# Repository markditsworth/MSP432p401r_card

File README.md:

# MSP432p401r Card

### PCB for a vertically mounted MSP432p401r chip

Uses the Samtec MECF-50-01-L-DV polarized edge connector, or equivalent.

1.6mm board thickness.

Supports GPIO ports 1 through 6.

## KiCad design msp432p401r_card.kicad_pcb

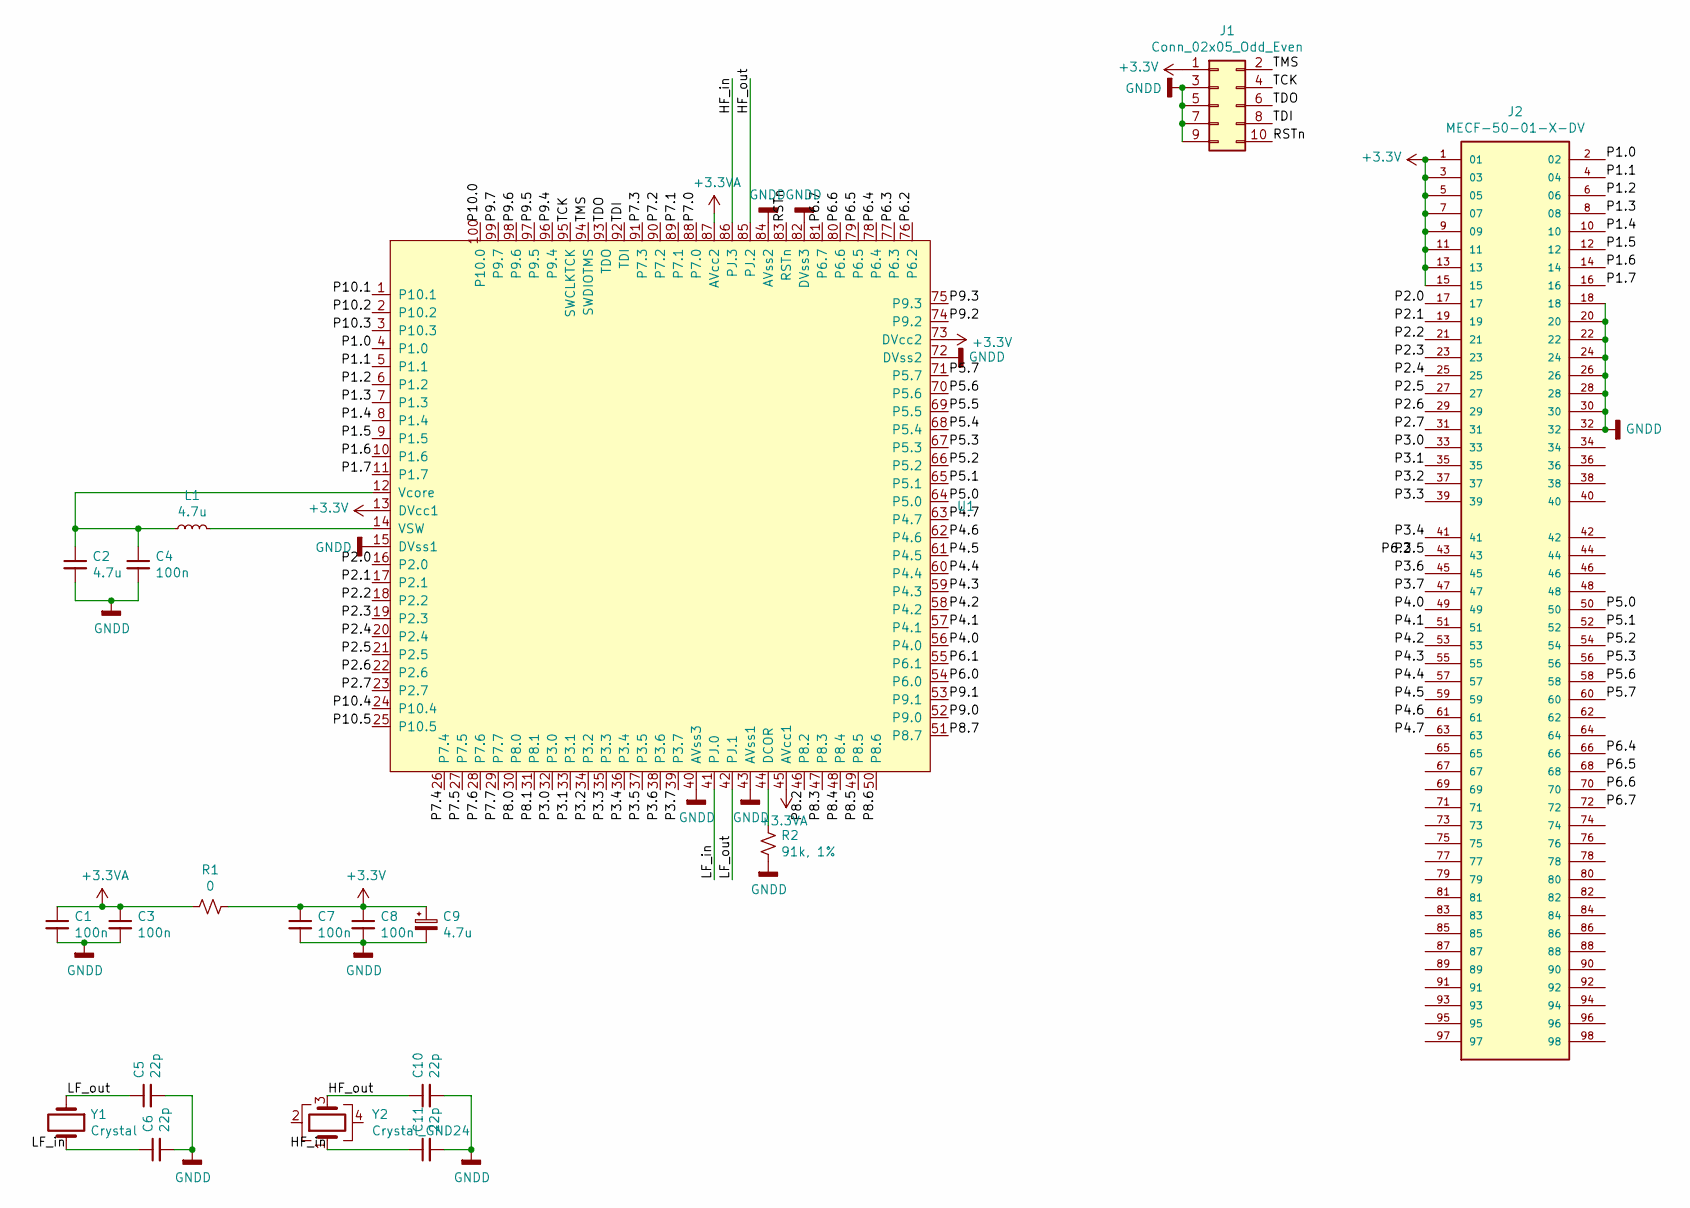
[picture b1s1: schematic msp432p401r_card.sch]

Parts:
C1, C3, C4, C7, C8: 100n; C_0402_1005Metric
C2, C9: 4.7u; C_1206_3216Metric
C5, C6, C10, C11: 22p; C_0402_1005Metric
J1: Conn_02x05_Odd_Even; Samtec_HLE-105-02-xx-DV-TE_2x05_P2.54mm_Horizontal
J2: MECF-50-01-X-DV; Samtec_MECF-50-0_-L-DV_2x50_P1.27mm_Polarized_Edge; PARTREV D
L1: 4.7u; L_2010_5025Metric; Part No LQM21PN4R7NGR
R1: 0; R_1206_3216Metric
R2: 91k, 1%; R_1206_3216Metric
U1: MSP432p401r_chip; LQFP-100_14x14mm_P0.5mm
Y1: Crystal; Crystal_SMD_MicroCrystal_MS3V-T1R
Y2: Crystal_GND24; Crystal_SMD_SeikoEpson_FA238-4Pin_3.2x2.5mm_HandSoldering

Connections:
+3.3VA: C1.1, C3.1, R1.2, U1.45 (AVcc1), U1.87 (AVcc2)
+3V3: C7.1, C8.1, C9.1, J1.1, J2.1, J2.3, J2.5, J2.7, J2.9, J2.11, J2.13, J2.15, R1.1, U1.13 (DVcc1), U1.73 (DVcc2)
/HF_in: C11.1, U1.86 (PJ.3), Y2.1
/HF_out: C10.1, U1.85 (PJ.2), Y2.3
/LF_in: C6.1, U1.41 (PJ.0), Y1.2
/LF_out: C5.1, U1.42 (PJ.1), Y1.1
/P1.0: J2.2, U1.4 (P1.0)
/P1.1: J2.4, U1.5 (P1.1)
/P1.2: J2.6, U1.6 (P1.2)
/P1.3: J2.8, U1.7 (P1.3)
/P1.4: J2.10, U1.8 (P1.4)
/P1.5: J2.12, U1.9 (P1.5)
/P1.6: J2.14, U1.10 (P1.6)
/P1.7: J2.16, U1.11 (P1.7)
/P2.0: J2.17, U1.16 (P2.0)
/P2.1: J2.19, U1.17 (P2.1)
/P2.2: J2.21, U1.18 (P2.2)
/P2.3: J2.23, U1.19 (P2.3)
/P2.4: J2.25, U1.20 (P2.4)
/P2.5: J2.27, U1.21 (P2.5)
/P2.6: J2.29, U1.22 (P2.6)
/P2.7: J2.31, U1.23 (P2.7)
/P3.0: J2.33, U1.32 (P3.0)
/P3.1: J2.35, U1.33 (P3.1)
/P3.2: J2.37, U1.34 (P3.2)
/P3.3: J2.39, U1.35 (P3.3)
/P3.4: J2.41, U1.36 (P3.4)
/P3.5: J2.43, U1.37 (P3.5)
/P3.6: J2.45, U1.38 (P3.6)
/P3.7: J2.47, U1.39 (P3.7)
/P4.0: J2.49, U1.56 (P4.0)
/P4.1: J2.51, U1.57 (P4.1)
/P4.2: J2.53, U1.58 (P4.2)
/P4.3: J2.55, U1.59 (P4.3)
/P4.4: J2.57, U1.60 (P4.4)
/P4.5: J2.59, U1.61 (P4.5)
/P4.6: J2.61, U1.62 (P4.6)
/P4.7: J2.63, U1.63 (P4.7)
/P5.0: J2.50, U1.64 (P5.0)
/P5.1: J2.52, U1.65 (P5.1)
/P5.2: J2.54, U1.66 (P5.2)
/P5.3: J2.56, U1.67 (P5.3)
/P5.4: U1.68 (P5.4)
/P5.5: U1.69 (P5.5)
/P5.6: J2.58, U1.70 (P5.6)
/P5.7: J2.60, U1.71 (P5.7)
/P6.0: U1.54 (P6.0)
/P6.1: U1.55 (P6.1)
/P6.2: U1.76 (P6.2)
/P6.3: U1.77 (P6.3)
/P6.4: J2.66, U1.78 (P6.4)
/P6.5: J2.68, U1.79 (P6.5)
/P6.6: J2.70, U1.80 (P6.6)
/P6.7: J2.72, U1.81 (P6.7)
/P7.0: U1.88 (P7.0)
/P7.1: U1.89 (P7.1)
/P7.2: U1.90 (P7.2)
/P7.3: U1.91 (P7.3)
/P7.4: U1.26 (P7.4)
/P7.5: U1.27 (P7.5)
/P7.6: U1.28 (P7.6)
/P7.7: U1.29 (P7.7)
/P8.0: U1.30 (P8.0)
/P8.1: U1.31 (P8.1)
/P8.2: U1.46 (P8.2)
/P8.3: U1.47 (P8.3)
/P8.4: U1.48 (P8.4)
/P8.5: U1.49 (P8.5)
/P8.6: U1.50 (P8.6)
/P8.7: U1.51 (P8.7)
/P9.0: U1.52 (P9.0)
/P9.1: U1.53 (P9.1)
/P9.2: U1.74 (P9.2)
/P9.3: U1.75 (P9.3)
/P9.4: U1.96 (P9.4)
/P9.5: U1.97 (P9.5)
/P9.6: U1.98 (P9.6)
/P9.7: U1.99 (P9.7)
/P10.0: U1.100 (P10.0)
/P10.1: U1.1 (P10.1)
/P10.2: U1.2 (P10.2)
/P10.3: U1.3 (P10.3)
/P10.4: U1.24 (P10.4)
/P10.5: U1.25 (P10.5)
/RSTn: J1.10, U1.83 (RSTn)
/TCK: J1.4, U1.95 (SWCLKTCK)
/TDI: J1.8, U1.92 (TDI)
/TDO: J1.6, U1.93 (TDO)
/TMS: J1.2, U1.94 (SWDIOTMS)
GNDD: C1.2, C2.2, C3.2, C4.2, C5.2, C6.2, C7.2, C8.2, C9.2, C10.2, C11.2, J1.3, J1.5, J1.7, J1.9, J2.18, J2.20, J2.22, J2.24, J2.26, J2.28, J2.30, J2.32, R2.2, U1.15 (DVss1), U1.40 (AVss3), U1.43 (AVss1), U1.72 (DVss2), U1.82 (DVss3), U1.84 (AVss2)
unnamed: C2.1, C4.1, L1.1, U1.12 (Vcore)
unnamed: L1.2, U1.14 (VSW)
unnamed: R2.1, U1.44 (DCOR)

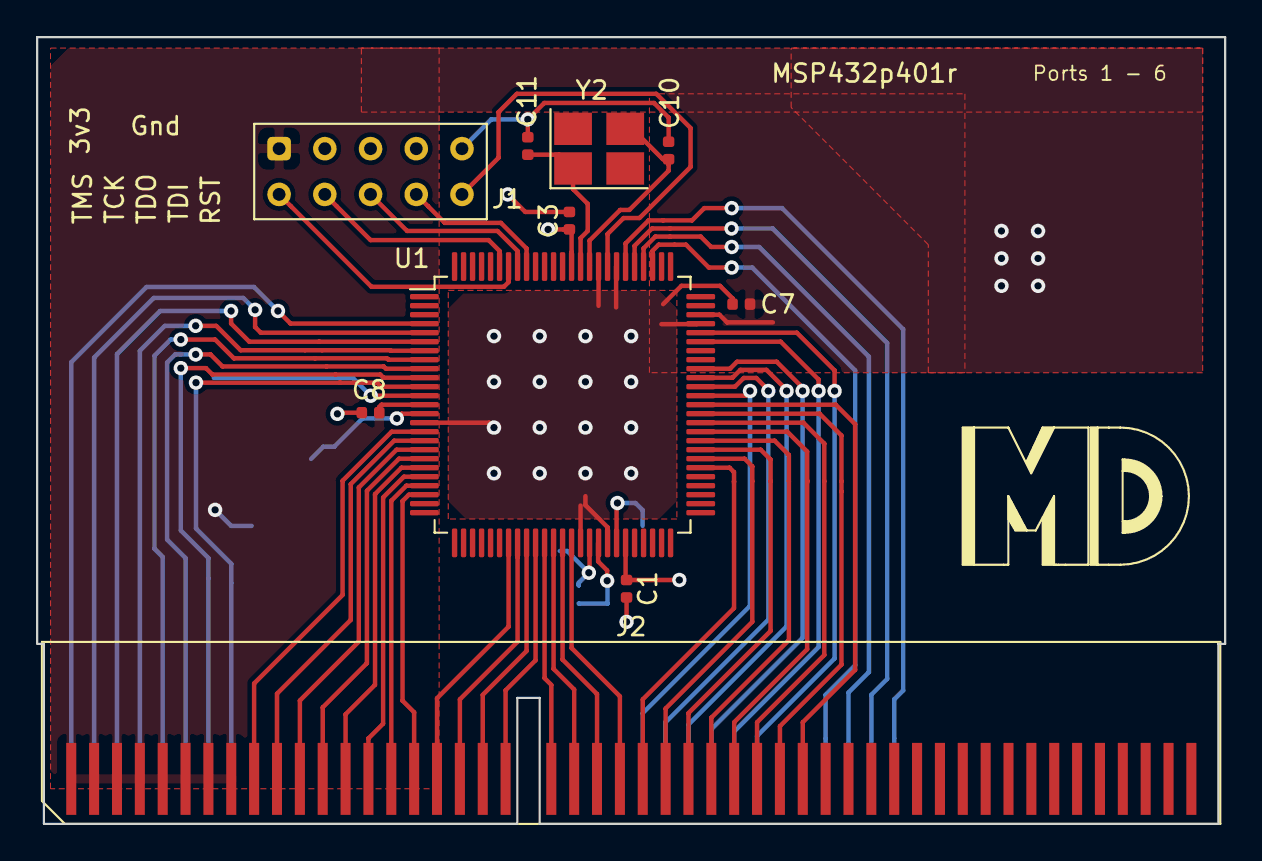
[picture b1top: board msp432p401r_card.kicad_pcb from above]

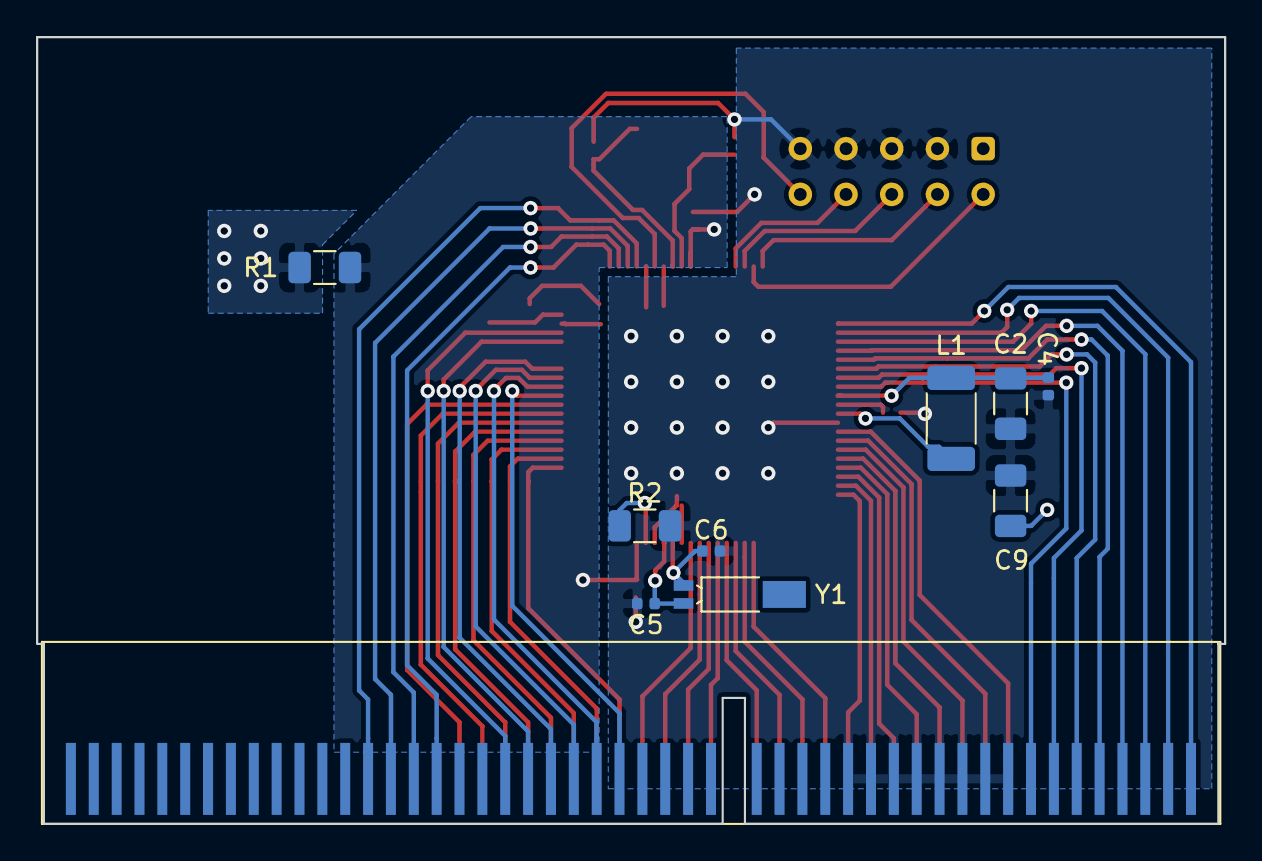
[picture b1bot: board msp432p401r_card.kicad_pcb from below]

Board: 2 copper layers, 66.0 x 43.7 mm, 19 parts (9 on the bottom side), 57 nets.

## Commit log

2020-12-03 add pcb image
